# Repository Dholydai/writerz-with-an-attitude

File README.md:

# writerz-with-an-attitude
Human-factored Post-Mechanical writing instruments designed for and approved by 'Writerz With an Attitude'.

Why are nascent writers, born in the third decade of the 21st century, being shackled to a 152-year-old 19th-Century mechanical typewriter interface?

I have used a Dvorak keyboard for thirty-five years. After two decades of typing, bad pains developed in my left hand and wrist. Analyzing 
my breakdown, I concluded that the physical layout of keys on conventional keyboards forces unnatural movements.

The typewriter keyboard is injurious, as evidenced by the long history of 'typists' developing carpal tunnel syndrome, including myself.

I designed the 'Dvorak 2026' to place the keys where the fingers of my two hands expect them to be. No more pain, writing is fun.

I contend that the Post-Mechanical variants establish a 'Nuevo Teclado Universal' standard. These human-factored designs will fit in currently produced
laptop PC cases. The forty-eight character keys make the keyboards ISO compliant, compatible with European languages.

I have created ISO compliant firmware, and designed Windows drivers for six European languages, so far. Work on Lixux keyd configurations will
begin. Apple drivers are not my wheelhouse. Collaboration from those who can write Apple drivers is expected.

Single-hand writers should have use of modern writing instruments. After World War 2 ended, LCDR Dvorak designed two practical single-hand letter 
schemes for the typewriter that enabled disabled veterans to type comfortably.

My new compact single-hand keyboard designs have a few notable tweaks, but do not stray far from the original designs. Both variants now share 
the same letter scheme. The left-hand and right-hand keyboards are mirror images of each other.

Quality of key switches:

Cherry MX switches have great quality. Never had a problem with them. I build all of my keyboards with Cherry switches. Less costly switches from other
manufacturers that I have tried are not shaped consistantly. Those switches would not fit the tight tolerances of my case tops. The stems tilted this
way and that way.

Availability of keycap sets:

I have been subsituting common keycaps sizes for the exotic sizes required. I bought large XDA keycap sets, and relabeled selected keycaps with 
keyboard stickers as needed.

Finding a 6U spacebar is difficult. My source makes spacebars with the stem 1\2U offset. I have designed alternate case top sections to accommodate that
spacebar. My PCBs have a dual position switch footprint to accommodate either centered or offset spacebar switch.

YUZU... In May 2025 I found a die-sub keycap manufacturer that makes one-off custom sets. The Prusa orange Maxmius above is populated by one of the many
austere sets I have created. I have designed and purchased nine keycaps sets from YUZU, including Spanish(Spain), Portuguese(Brazil), and BÉPO(France).

YUZU custom keycaps will make any die-sub keycap set that your heart desires. Common sizes still have to be sustituted. Being able to choose keycap 
sizes, colors, and legends is wonderful. Love the new Penguin Slide Belly (PBS) profile keycaps. Great price and quality.

The French, Spanish, and Brazilian keyboards were built in late August 2026.

3D printer problems:

The first Maximus case would not sit flat on a desktop. After a month of struggle to solve the problem, I reluctantly concluded that:

1. My Voron Trident 350 cannot print case top sections with enough quality. The X- to Y-axis geometry is not consistently 90 degrees.
2. This problem is not Voron Designs' shortcoming, it is intrinsic to all Core-XY printers. This is due to the quick changes of direction that temporarily stretch the long XY belts during operation; that slop gets worse as printer size increases.
3. 'Bed slingers' use much shorter belts, they do not have this built-in fault.

My Prusa MK3.5 has a new companion... a Prusa MK4S. The new printer makes parts that match-up perfectly with the MK 3.5 parts. Print times for a case
bottom section changed dramatically: from 3hs 15 mins to 1 hr 45 mins. I am now a committed Prusa fanatic.

Link to my repo of custom KiCad libraries: [MX Switch Custom](https://github.com/Dholydai/mx-switch-custom)

Ronald Earl Walker - Inventor of the Post-Mechanical Keyboard

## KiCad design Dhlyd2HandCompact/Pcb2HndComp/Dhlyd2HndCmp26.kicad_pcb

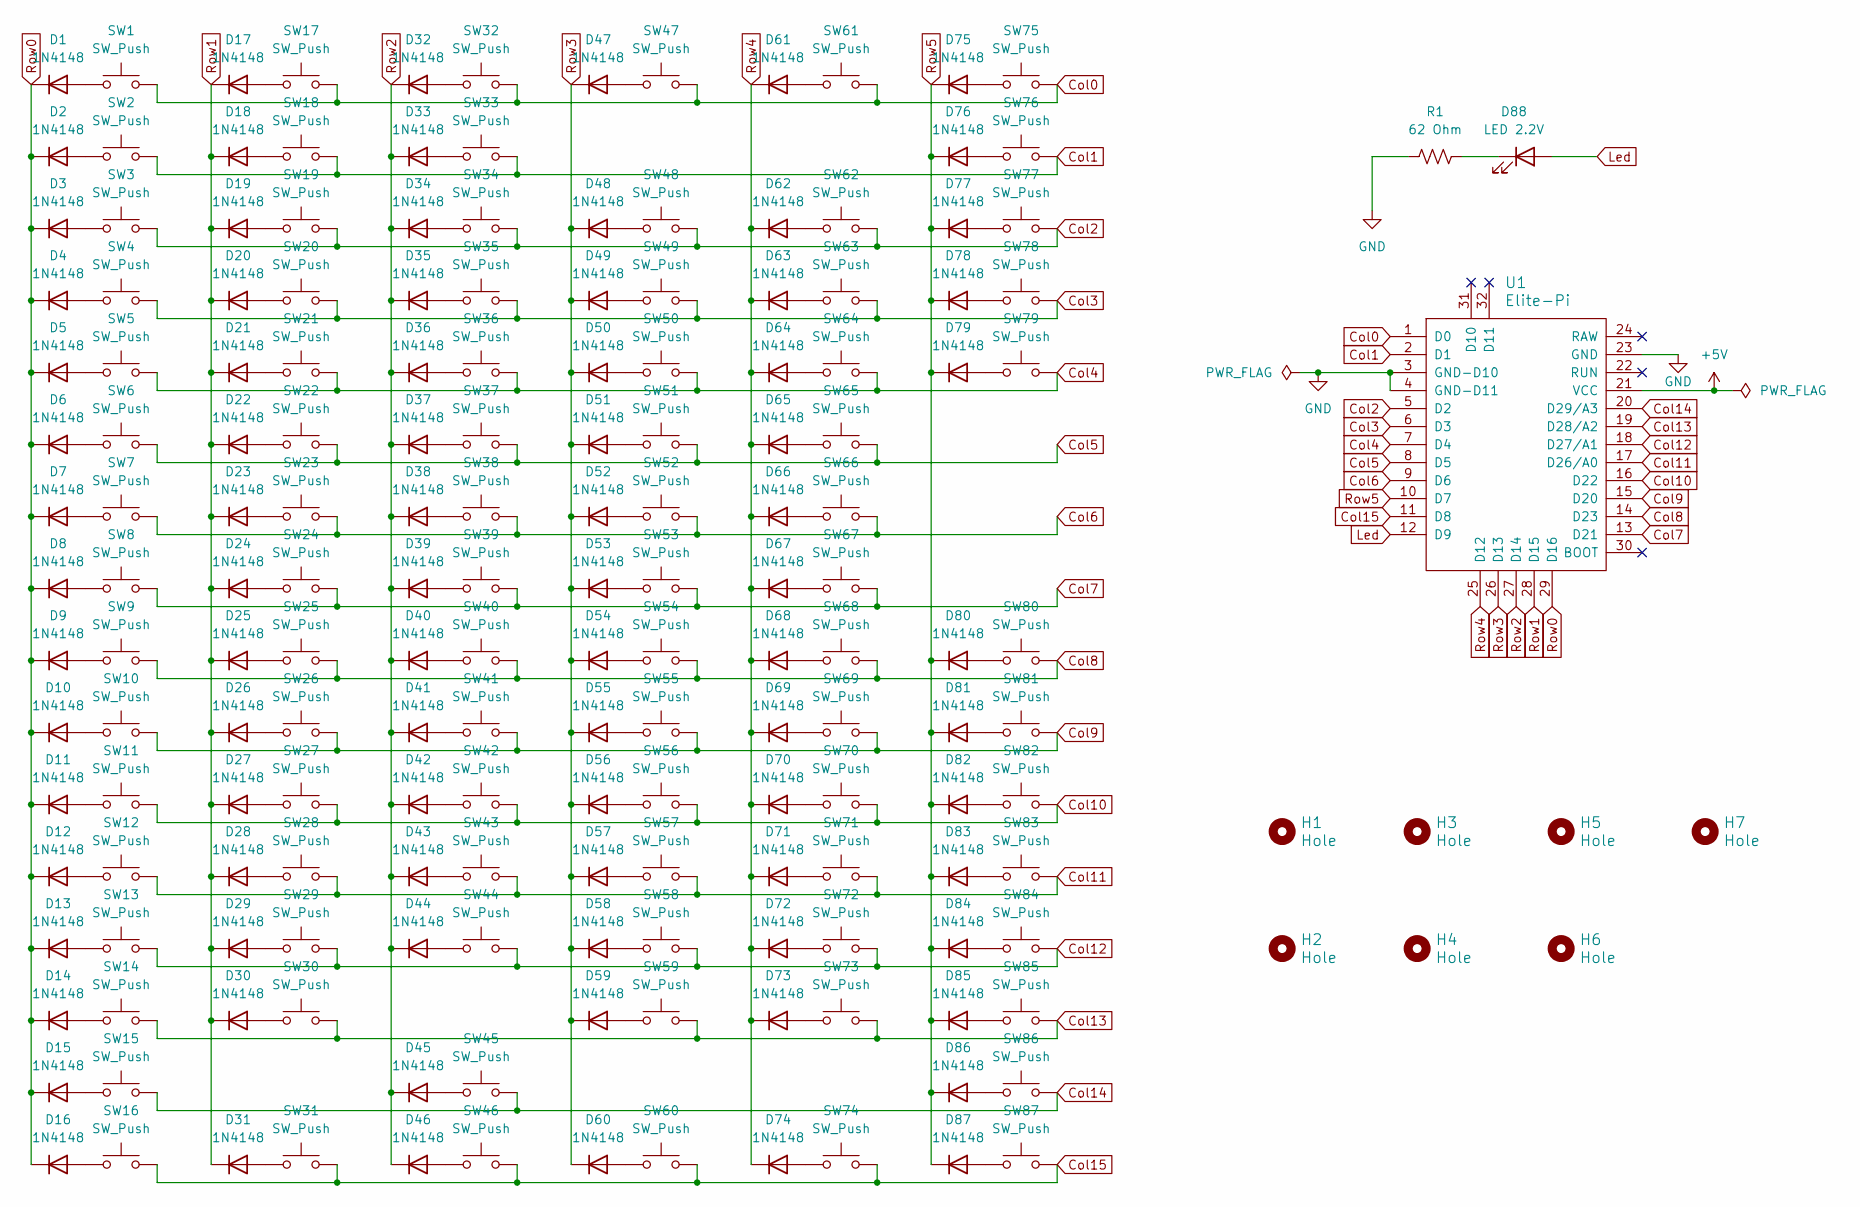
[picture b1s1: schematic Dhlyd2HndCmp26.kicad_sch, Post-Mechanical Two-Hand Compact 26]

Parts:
D1, D2, D3, D4, D5, D6, D7, D8, D9, D10, D11, D12, D13, D14, D15, D16, D17, D18, D19, D20, D21, D22, D23, D24, D25, D26, D27, D28, D29, D30, D31, D32, D33, D34, D35, D36, D37, D38, D39, D40, D41, D42, D43, D44, D45, D46, D47, D48, D49, D50, D51, D52, D53, D54, D55, D56, D57, D58, D59, D60, D61, D62, D63, D64, D65, D66, D67, D68, D69, D70, D71, D72, D73, D74, D75, D76, D77, D78, D79, D80, D81, D82, D83, D84, D85, D86, D87: 1N4148; D_DO-35_SOD27_P7.62mm_Horizontal
D88: LED 2.2V; SW_Ch_MX_LED_Template
H1, H2, H3, H4, H5, H6, H7: Hole; MountingHole_3.2mm_M3_Pad
R1: 62 Ohm; R_Axial_DIN0207_L6.3mm_D2.5mm_P10.16mm_Horizontal
SW1, SW2, SW3, SW4, SW5, SW6, SW7, SW8, SW9, SW10, SW11, SW12, SW13, SW14, SW15, SW16, SW18, SW19, SW20, SW21, SW22, SW23, SW24, SW25, SW26, SW27, SW28, SW29, SW31, SW33, SW34, SW35, SW36, SW37, SW38, SW39, SW40, SW41, SW42, SW43, SW44, SW46, SW48, SW49, SW50, SW51, SW52, SW54, SW55, SW56, SW57, SW58, SW60, SW62, SW63, SW64, SW65, SW66, SW68, SW69, SW70, SW71, SW72, SW74, SW76, SW77, SW81, SW83, SW84, SW85, SW86, SW87: SW_Push; SW_Cherry_MX_1.00u_PCB
SW17, SW30, SW61, SW73: SW_Push; SW_Cherry_MX_1.50u_PCB
SW32, SW45: SW_Push; SW_Cherry_MX_1.1666u_PCB
SW47, SW59: SW_Push; SW_Cherry_MX_1.6666u_PCB
SW53: SW_Push; SW_Cherry_MX_1.3333u_PCB
SW67: SW_Push; SW_Ch_Inv_MX_2.00u_PCB
SW75, SW78, SW80, SW82: SW_Push; SW_Cherry_MX_1.25u_PCB
SW79: SW_Push; SW_Ch_Inv_MX_6.00u_PCB_Stagger
U1: Elite-Pi

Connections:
+5V: U1.21 (VCC)
Col0: SW1.2, SW17.2, SW32.2, SW47.2, SW61.2, SW75.2, U1.1 (D0)
Col1: SW2.2, SW18.2, SW33.2, SW76.2, U1.2 (D1)
Col2: SW3.2, SW19.2, SW34.2, SW48.2, SW62.2, SW77.2, U1.5 (D2)
Col3: SW4.2, SW20.2, SW35.2, SW49.2, SW63.2, SW78.2, U1.6 (D3)
Col4: SW5.2, SW21.2, SW36.2, SW50.2, SW64.2, SW79.2, U1.7 (D4)
Col5: SW6.2, SW22.2, SW37.2, SW51.2, SW65.2, U1.8 (D5)
Col6: SW7.2, SW23.2, SW38.2, SW52.2, SW66.2, U1.9 (D6)
Col7: SW8.2, SW24.2, SW39.2, SW53.2, SW67.2, U1.13 (D21)
Col8: SW9.2, SW25.2, SW40.2, SW54.2, SW68.2, SW80.2, U1.14 (D23)
Col9: SW10.2, SW26.2, SW41.2, SW55.2, SW69.2, SW81.2, U1.15 (D20)
Col10: SW11.2, SW27.2, SW42.2, SW56.2, SW70.2, SW82.2, U1.16 (D22)
Col11: SW12.2, SW28.2, SW43.2, SW57.2, SW71.2, SW83.2, U1.17 (D26/A0)
Col12: SW13.2, SW29.2, SW44.2, SW58.2, SW72.2, SW84.2, U1.18 (D27/A1)
Col13: SW14.2, SW30.2, SW59.2, SW73.2, SW85.2, U1.19 (D28/A2)
Col14: SW15.2, SW45.2, SW86.2, U1.20 (D29/A3)
Col15: SW16.2, SW31.2, SW46.2, SW60.2, SW74.2, SW87.2, U1.11 (D8)
GND: R1.1, U1.3 (GND-D10), U1.4 (GND-D11), U1.23 (GND)
Led: D88.2 (A), U1.12 (D9)
unnamed: D1.2 (A), SW1.1
unnamed: D2.2 (A), SW2.1
unnamed: D3.2 (A), SW3.1
unnamed: D4.2 (A), SW4.1
unnamed: D5.2 (A), SW5.1
unnamed: D6.2 (A), SW6.1
unnamed: D7.2 (A), SW7.1
unnamed: D8.2 (A), SW8.1
unnamed: D9.2 (A), SW9.1
unnamed: D10.2 (A), SW10.1
unnamed: D11.2 (A), SW11.1
unnamed: D12.2 (A), SW12.1
unnamed: D13.2 (A), SW13.1
unnamed: D14.2 (A), SW14.1
unnamed: D15.2 (A), SW15.1
unnamed: D16.2 (A), SW16.1
unnamed: D17.2 (A), SW17.1
unnamed: D18.2 (A), SW18.1
unnamed: D19.2 (A), SW19.1
unnamed: D20.2 (A), SW20.1
unnamed: D21.2 (A), SW21.1
unnamed: D22.2 (A), SW22.1
unnamed: D23.2 (A), SW23.1
unnamed: D24.2 (A), SW24.1
unnamed: D25.2 (A), SW25.1
unnamed: D26.2 (A), SW26.1
unnamed: D27.2 (A), SW27.1
unnamed: D28.2 (A), SW28.1
unnamed: D29.2 (A), SW29.1
unnamed: D30.2 (A), SW30.1
unnamed: D31.2 (A), SW31.1
unnamed: D32.2 (A), SW32.1
unnamed: D33.2 (A), SW33.1
unnamed: D34.2 (A), SW34.1
unnamed: D35.2 (A), SW35.1
unnamed: D36.2 (A), SW36.1
unnamed: D37.2 (A), SW37.1
unnamed: D38.2 (A), SW38.1
unnamed: D39.2 (A), SW39.1
unnamed: D40.2 (A), SW40.1
unnamed: D41.2 (A), SW41.1
unnamed: D42.2 (A), SW42.1
unnamed: D43.2 (A), SW43.1
unnamed: D44.2 (A), SW44.1
unnamed: D45.2 (A), SW45.1
unnamed: D46.2 (A), SW46.1
unnamed: D47.2 (A), SW47.1
unnamed: D48.2 (A), SW48.1
unnamed: D49.2 (A), SW49.1
unnamed: D50.2 (A), SW50.1
unnamed: D51.2 (A), SW51.1
unnamed: D52.2 (A), SW52.1
unnamed: D53.2 (A), SW53.1
unnamed: D54.2 (A), SW54.1
unnamed: D55.2 (A), SW55.1
unnamed: D56.2 (A), SW56.1
unnamed: D57.2 (A), SW57.1
unnamed: D58.2 (A), SW58.1
unnamed: D59.2 (A), SW59.1
unnamed: D60.2 (A), SW60.1
unnamed: D61.2 (A), SW61.1
unnamed: D62.2 (A), SW62.1
unnamed: D63.2 (A), SW63.1
unnamed: D64.2 (A), SW64.1
unnamed: D65.2 (A), SW65.1
unnamed: D66.2 (A), SW66.1
unnamed: D67.2 (A), SW67.1
unnamed: D68.2 (A), SW68.1
unnamed: D69.2 (A), SW69.1
unnamed: D70.2 (A), SW70.1
unnamed: D71.2 (A), SW71.1
unnamed: D72.2 (A), SW72.1
unnamed: D73.2 (A), SW73.1
unnamed: D74.2 (A), SW74.1
unnamed: D75.2 (A), SW75.1
unnamed: D76.2 (A), SW76.1
unnamed: D77.2 (A), SW77.1
unnamed: D78.2 (A), SW78.1
unnamed: D79.2 (A), SW79.1
unnamed: D80.2 (A), SW80.1
unnamed: D81.2 (A), SW81.1
unnamed: D82.2 (A), SW82.1
unnamed: D83.2 (A), SW83.1
unnamed: D84.2 (A), SW84.1
unnamed: D85.2 (A), SW85.1
unnamed: D86.2 (A), SW86.1
unnamed: D87.2 (A), SW87.1
unnamed: D88.1 (K), R1.2
Row0: D1.1 (K), D2.1 (K), D3.1 (K), D4.1 (K), D5.1 (K), D6.1 (K), D7.1 (K), D8.1 (K), D9.1 (K), D10.1 (K), D11.1 (K), D12.1 (K), D13.1 (K), D14.1 (K), D15.1 (K), D16.1 (K), U1.29 (D16)
Row1: D17.1 (K), D18.1 (K), D19.1 (K), D20.1 (K), D21.1 (K), D22.1 (K), D23.1 (K), D24.1 (K), D25.1 (K), D26.1 (K), D27.1 (K), D28.1 (K), D29.1 (K), D30.1 (K), D31.1 (K), U1.28 (D15)
Row2: D32.1 (K), D33.1 (K), D34.1 (K), D35.1 (K), D36.1 (K), D37.1 (K), D38.1 (K), D39.1 (K), D40.1 (K), D41.1 (K), D42.1 (K), D43.1 (K), D44.1 (K), D45.1 (K), D46.1 (K), U1.27 (D14)
Row3: D47.1 (K), D48.1 (K), D49.1 (K), D50.1 (K), D51.1 (K), D52.1 (K), D53.1 (K), D54.1 (K), D55.1 (K), D56.1 (K), D57.1 (K), D58.1 (K), D59.1 (K), D60.1 (K), U1.26 (D13)
Row4: D61.1 (K), D62.1 (K), D63.1 (K), D64.1 (K), D65.1 (K), D66.1 (K), D67.1 (K), D68.1 (K), D69.1 (K), D70.1 (K), D71.1 (K), D72.1 (K), D73.1 (K), D74.1 (K), U1.25 (D12)
Row5: D75.1 (K), D76.1 (K), D77.1 (K), D78.1 (K), D79.1 (K), D80.1 (K), D81.1 (K), D82.1 (K), D83.1 (K), D84.1 (K), D85.1 (K), D86.1 (K), D87.1 (K), U1.10 (D7)

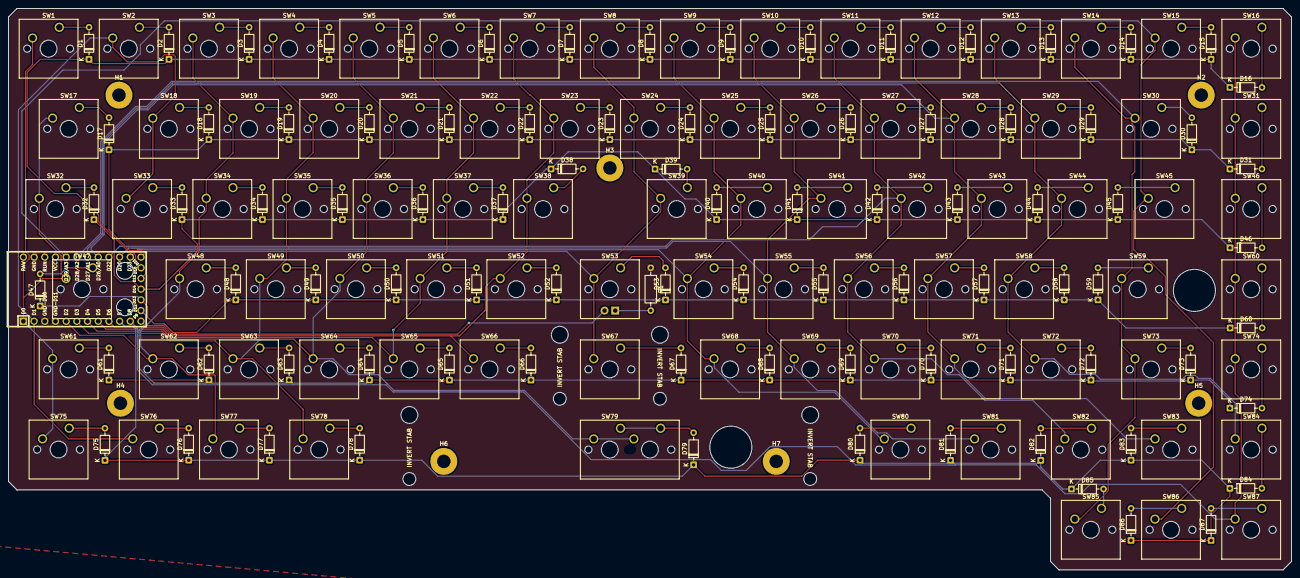
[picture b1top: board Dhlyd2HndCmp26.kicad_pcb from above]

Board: 2 copper layers, 304.8 x 133.4 mm, 184 parts (0 on the bottom side), 112 nets.
